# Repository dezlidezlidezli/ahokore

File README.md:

# ahokore

Ahokore is a 36-key one-piece split keyboard, with full wireless functionality. Stagger is copied from the Ferris, as I found that very comfortable. The name is "wireless" translated into Maori.

V1 is tested to be fully working, and uses a nice!nano.

V2 has been tested and is fully working, and a small group-buy has been run. Extras will be available within a few weeks (written on 30/6/21), on store.dez.li.

If you'd like to produce the board yourself, or modify these files, I reccomend using the v2-fantail

All work in this repository is released into the public domain. See the license file for more details!

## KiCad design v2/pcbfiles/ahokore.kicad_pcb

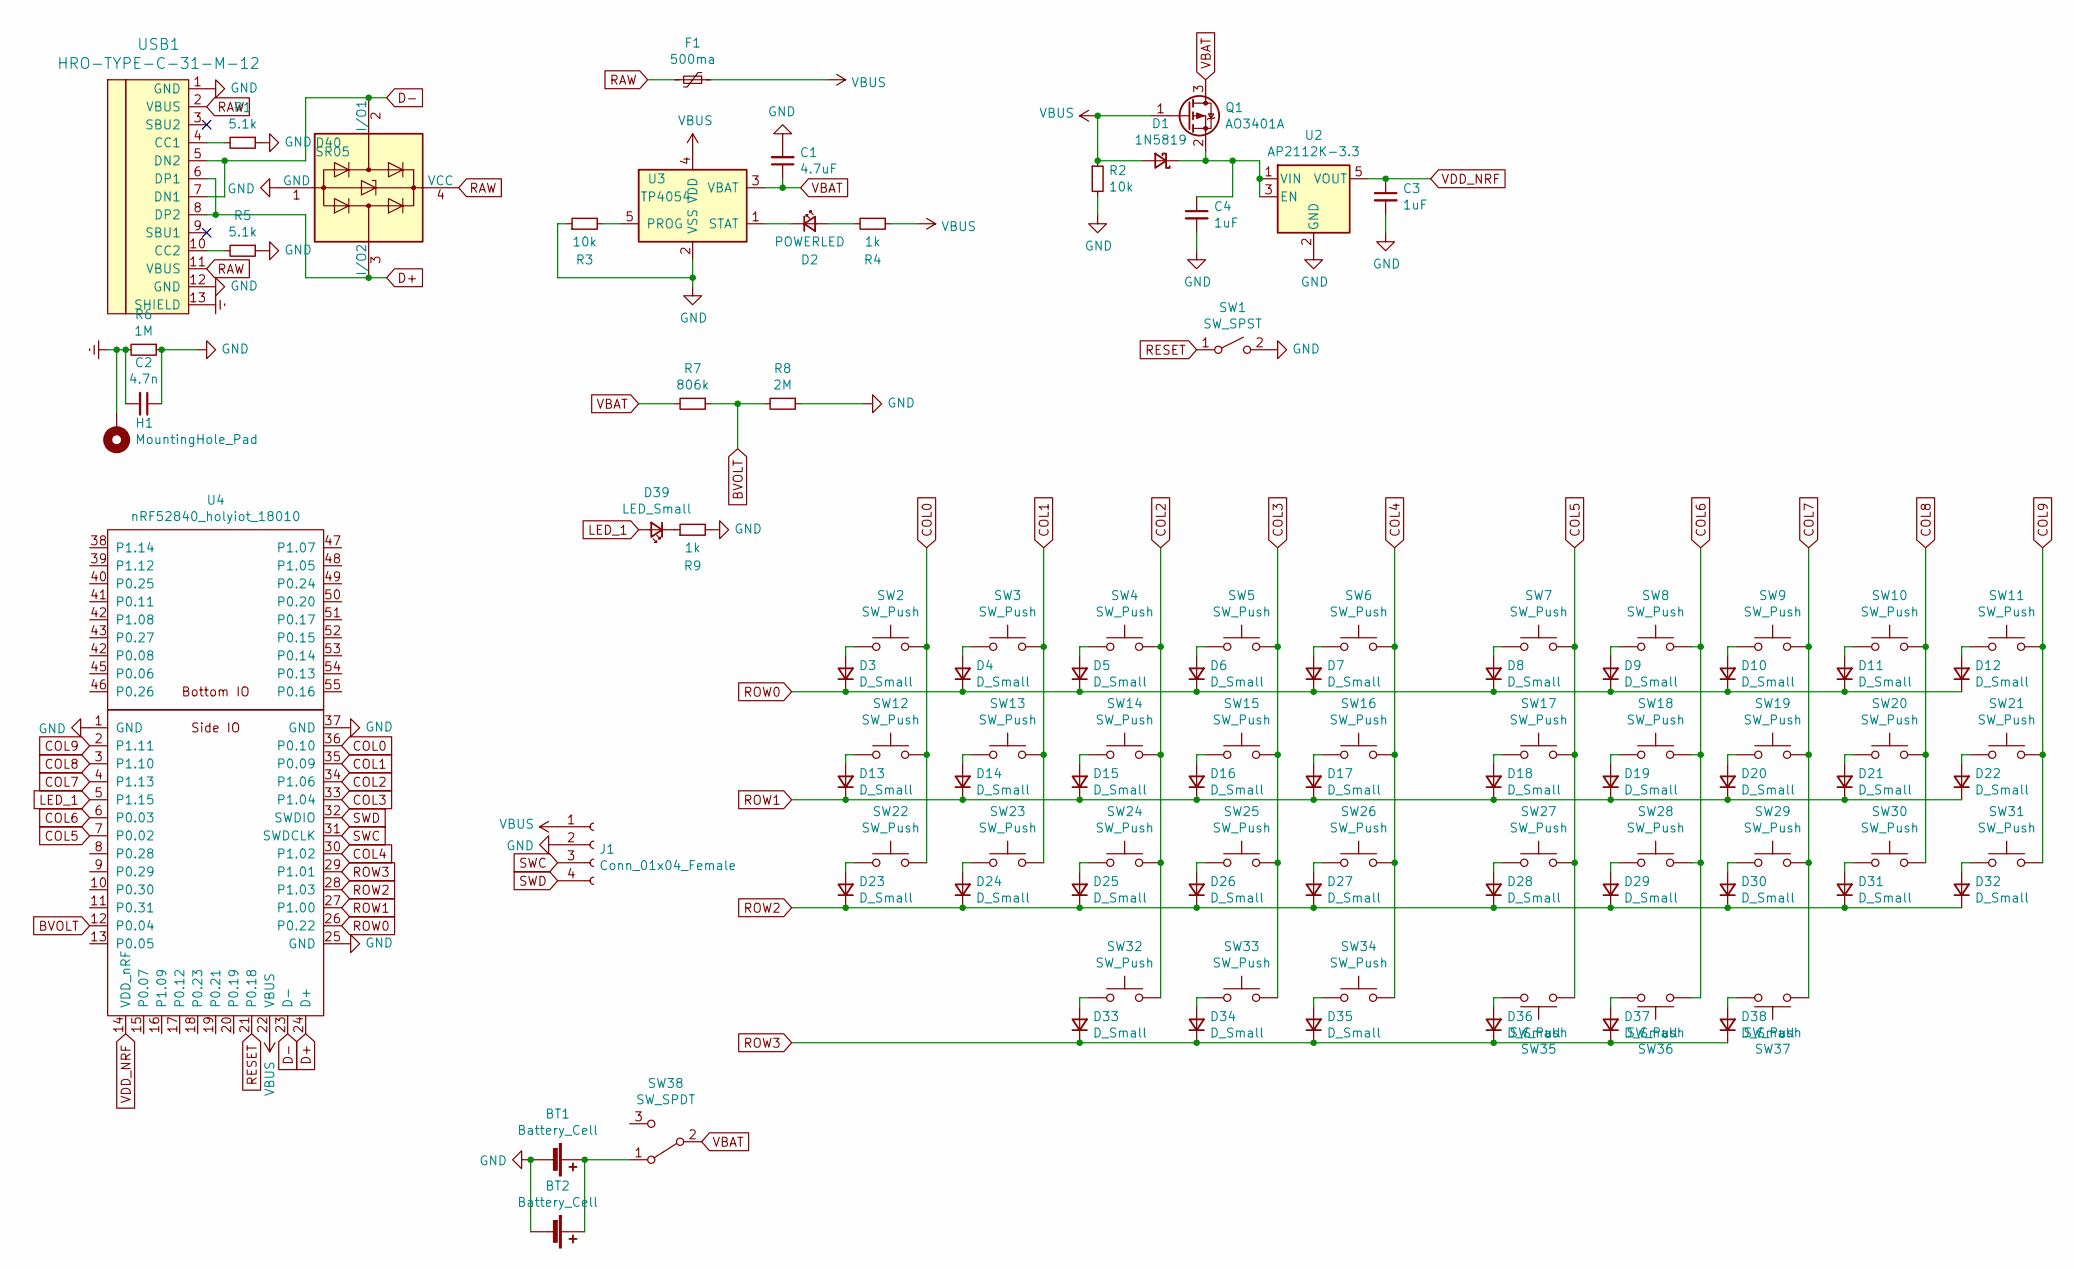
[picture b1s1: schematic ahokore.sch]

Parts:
BT1: Battery_Cell; JST_PH_S2B-PH-K_1x02_P2.00mm_Horizontal
BT2: Battery_Cell; custombatteryconnector
C1: 4.7uF; C_0805_2012Metric
C2: 4.7n; C_1206_3216Metric
C3, C4: 1uF; C_0805_2012Metric
D1: 1N5819; D_SOD-123
D2: POWERLED; D_0805_2012Metric
D3, D4, D5, D6, D7, D8, D9, D10, D11, D12, D13, D14, D15, D16, D17, D18, D19, D20, D21, D22, D23, D24, D25, D26, D27, D28, D29, D30, D31, D32, D33, D34, D35, D36, D37, D38: D_Small; D_SOD-123
D39: LED_Small; D_0805_2012Metric
D40: SR05; SOT-143
F1: 500ma; Fuse_1206_3216Metric
H1: MountingHole_Pad
J1: Conn_01x04_Female; PinHeader_1x04_P2.54mm_Vertical
Q1: AO3401A; SOT-23
R1, R5: 5.1k; R_0805_2012Metric
R2, R3: 10k; R_0805_2012Metric
R4, R9: 1k; R_0805_2012Metric
R6: 1M; R_0805_2012Metric
R7: 806k; R_0805_2012Metric
R8: 2M; R_0805_2012Metric
SW1: SW_SPST; custom-reset-switch
SW2, SW3, SW4, SW5, SW6, SW7, SW8, SW9, SW10, SW11, SW12, SW13, SW14, SW15, SW16, SW17, SW18, SW19, SW20, SW21, SW22, SW23, SW24, SW25, SW26, SW27, SW28, SW29, SW30, SW31, SW32, SW33, SW34, SW35, SW36, SW37: SW_Push; Choc_PG1350_Choc_Spacing
SW38: SW_SPDT; OS102011MA1QN1
U2: AP2112K-3.3; SOT-23-5
U3: TP4054; SOT-23-5
U4: nRF52840_holyiot_18010
USB1: HRO-TYPE-C-31-M-12; HRO-TYPE-C-31-M-12-HandSoldering

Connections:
BVOLT: R7.1, R8.2, U4.12 (P0.04)
COL0: SW2.2, SW12.2, SW22.2, U4.36 (P0.10)
COL1: SW3.2, SW13.2, SW23.2, U4.35 (P0.09)
COL2: SW4.2, SW14.2, SW24.2, SW32.2, U4.34 (P1.06)
COL3: SW5.2, SW15.2, SW25.2, SW33.2, U4.33 (P1.04)
COL4: SW6.2, SW16.2, SW26.2, SW34.2, U4.30 (P1.02)
COL5: SW7.2, SW17.2, SW27.2, SW35.1, U4.7 (P0.02)
COL6: SW8.2, SW18.2, SW28.2, SW36.1, U4.6 (P0.03)
COL7: SW9.2, SW19.2, SW29.2, SW37.1, U4.4 (P1.13)
COL8: SW10.2, SW20.2, SW30.2, U4.3 (P1.10)
COL9: SW11.2, SW21.2, SW31.2, U4.2 (P1.11)
D+: D40.3 (I/O2), U4.24 (D+), USB1.6 (DP1), USB1.8 (DP2)
D-: D40.2 (I/O1), U4.23 (D-), USB1.5 (DN2), USB1.7 (DN1)
Earth: C2.2, H1.1, R6.2, SW38.0, USB1.13 (SHIELD)
GND: BT1.2 (-), BT2.2 (-), C1.2, C2.1, C3.2, C4.2, D40.1 (GND), J1.2, R1.1, R2.2, R3.1, R5.1, R6.1, R8.1, R9.2, SW1.2 (B), U2.2 (GND), U3.2 (VSS), U4.1 (GND), U4.25 (GND), U4.37 (GND), USB1.1 (GND), USB1.12 (GND)
LED_1: D39.2 (A), U4.5 (P1.15)
unnamed: BT1.1 (+), BT2.1 (+), SW38.1 (A)
unnamed: C4.1, D1.1 (K), Q1.2 (S), U2.1 (VIN), U2.3 (EN)
unnamed: D2.1 (K), U3.1 (STAT)
unnamed: D2.2 (A), R4.2
unnamed: D3.2 (A), SW2.1
unnamed: D4.2 (A), SW3.1
unnamed: D5.2 (A), SW4.1
unnamed: D6.2 (A), SW5.1
unnamed: D7.2 (A), SW6.1
unnamed: D8.2 (A), SW7.1
unnamed: D9.2 (A), SW8.1
unnamed: D10.2 (A), SW9.1
unnamed: D11.2 (A), SW10.1
unnamed: D12.2 (A), SW11.1
unnamed: D13.2 (A), SW12.1
unnamed: D14.2 (A), SW13.1
unnamed: D15.2 (A), SW14.1
unnamed: D16.2 (A), SW15.1
unnamed: D17.2 (A), SW16.1
unnamed: D18.2 (A), SW17.1
unnamed: D19.2 (A), SW18.1
unnamed: D20.2 (A), SW19.1
unnamed: D21.2 (A), SW20.1
unnamed: D22.2 (A), SW21.1
unnamed: D23.2 (A), SW22.1
unnamed: D24.2 (A), SW23.1
unnamed: D25.2 (A), SW24.1
unnamed: D26.2 (A), SW25.1
unnamed: D27.2 (A), SW26.1
unnamed: D28.2 (A), SW27.1
unnamed: D29.2 (A), SW28.1
unnamed: D30.2 (A), SW29.1
unnamed: D31.2 (A), SW30.1
unnamed: D32.2 (A), SW31.1
unnamed: D33.2 (A), SW32.1
unnamed: D34.2 (A), SW33.1
unnamed: D35.2 (A), SW34.1
unnamed: D36.2 (A), SW35.2
unnamed: D37.2 (A), SW36.2
unnamed: D38.2 (A), SW37.2
unnamed: D39.1 (K), R9.1
unnamed: R1.2, USB1.4 (CC1)
unnamed: R3.2, U3.5 (PROG)
unnamed: R5.2, USB1.10 (CC2)
RAW: D40.4 (VCC), F1.2, USB1.2 (VBUS), USB1.11 (VBUS)
RESET: SW1.1 (A), U4.21 (P0.18)
ROW0: D3.1 (K), D4.1 (K), D5.1 (K), D6.1 (K), D7.1 (K), D8.1 (K), D9.1 (K), D10.1 (K), D11.1 (K), D12.1 (K), U4.26 (P0.22)
ROW1: D13.1 (K), D14.1 (K), D15.1 (K), D16.1 (K), D17.1 (K), D18.1 (K), D19.1 (K), D20.1 (K), D21.1 (K), D22.1 (K), U4.27 (P1.00)
ROW2: D23.1 (K), D24.1 (K), D25.1 (K), D26.1 (K), D27.1 (K), D28.1 (K), D29.1 (K), D30.1 (K), D31.1 (K), D32.1 (K), U4.28 (P1.03)
ROW3: D33.1 (K), D34.1 (K), D35.1 (K), D36.1 (K), D37.1 (K), D38.1 (K), U4.29 (P1.01)
SWC: J1.3, U4.31 (SWDCLK)
SWD: J1.4, U4.32 (SWDIO)
VBAT: C1.1, Q1.3 (D), R7.2, SW38.2 (B), U3.3 (VBAT)
VBUS: D1.2 (A), F1.1, J1.1, Q1.1 (G), R2.1, R4.1, U3.4 (VDD), U4.22 (VBUS)
VDD_NRF: C3.1, U2.5 (VOUT), U4.14 (VDD_nRF)

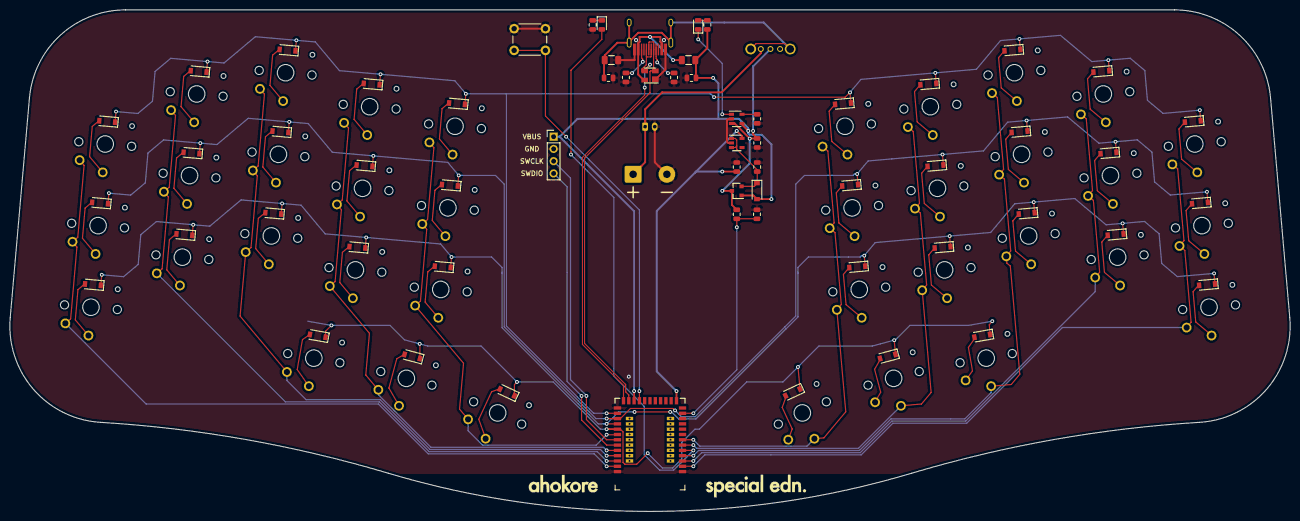
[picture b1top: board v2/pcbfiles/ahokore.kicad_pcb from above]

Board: 2 copper layers, 265.7 x 104.1 mm, 100 parts (0 on the bottom side), 71 nets.

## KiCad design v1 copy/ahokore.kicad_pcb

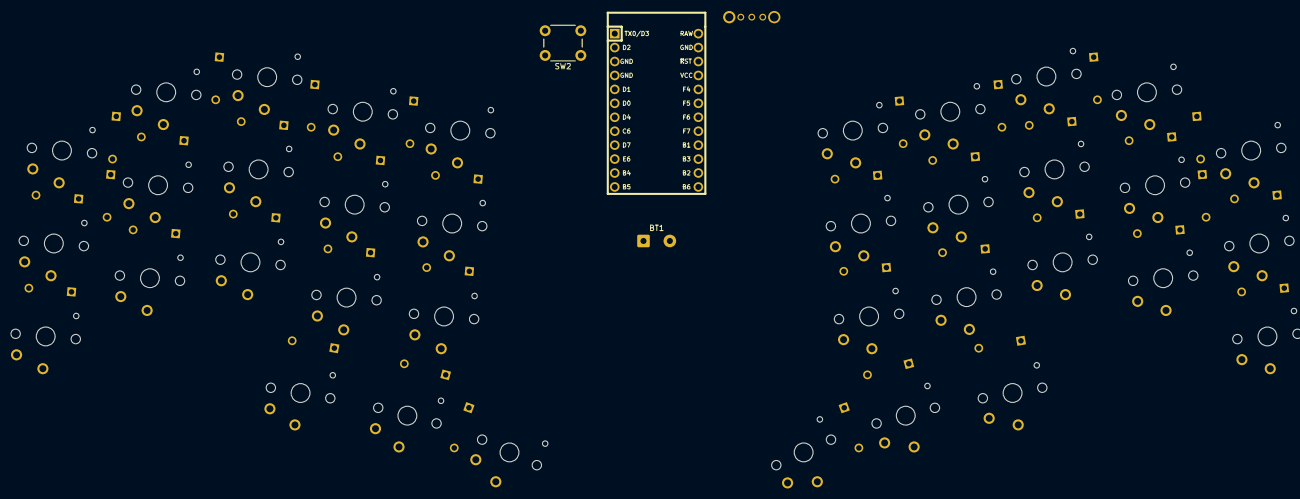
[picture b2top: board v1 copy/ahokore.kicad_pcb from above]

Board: 2 copper layers, 76 parts (0 on the bottom side), 54 nets, no tracks yet.

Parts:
BT1: Battery_Cell; battery
D1, D2, D3, D4, D5, D6, D7, D8, D9, D10, D11, D12, D13, D14, D15, D16, D17, D18, D19, D20, D21, D22, D23, D24, D25, D26, D27, D28, D29, D30, D31, D32, D33, D34, D35, D36: D_Small; Diode-Hybrid-Back
SW1: SW_SPDT; OS102011MA1QN1
SW2: SW_Push; SW_PUSH_6mm
SW3, SW4, SW5, SW6, SW7, SW8, SW9, SW10, SW11, SW12, SW13, SW14, SW15, SW16, SW17, SW18, SW19, SW20, SW21, SW22, SW23, SW24, SW25, SW26, SW27, SW28, SW29, SW30, SW31, SW32, SW33, SW34, SW35, SW36, SW37, SW38: SW_Push; Choc_PG1350_Choc_Spacing
U1: ProMicro; ArduinoProMicro

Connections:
+BATT: SW1.2, U1.24
COL0: SW3.2, SW13.2, SW23.2, U1.1
COL1: SW4.2, SW14.2, SW24.2, U1.2
COL2: SW5.2, SW15.2, SW25.2, SW33.2, U1.5
COL3: SW6.2, SW16.2, SW26.2, SW34.2, U1.6
COL4: SW7.2, SW17.2, SW27.2, SW35.2, U1.7
COL5: SW8.2, SW18.2, SW28.2, SW36.2, U1.20
COL6: SW9.2, SW19.2, SW29.2, SW37.2, U1.19
COL7: SW10.2, SW20.2, SW30.2, SW38.2, U1.18
COL8: SW11.2, SW21.2, SW31.2, U1.17
COL9: SW12.2, SW22.2, SW32.2, U1.16
GND: BT1.2, SW2.2, U1.3, U1.4, U1.23
unnamed: BT1.1, SW1.1
unnamed: D1.2, SW3.1
unnamed: D2.2, SW4.1
unnamed: D3.2, SW5.1
unnamed: D4.2, SW6.1
unnamed: D5.2, SW7.1
unnamed: D6.2, SW8.1
unnamed: D7.2, SW9.1
unnamed: D8.2, SW10.1
unnamed: D9.2, SW11.1
unnamed: D10.2, SW12.1
unnamed: D11.2, SW13.1
unnamed: D12.2, SW14.1
unnamed: D13.2, SW15.1
unnamed: D14.2, SW16.1
unnamed: D15.2, SW17.1
unnamed: D16.2, SW18.1
unnamed: D17.2, SW19.1
unnamed: D18.2, SW20.1
unnamed: D19.2, SW21.1
unnamed: D20.2, SW22.1
unnamed: D21.2, SW23.1
unnamed: D22.2, SW24.1
unnamed: D23.2, SW25.1
unnamed: D24.2, SW26.1
unnamed: D25.2, SW27.1
unnamed: D26.2, SW28.1
unnamed: D27.2, SW29.1
unnamed: D28.2, SW30.1
unnamed: D29.2, SW31.1
unnamed: D30.2, SW32.1
unnamed: D31.2, SW33.1
unnamed: D32.2, SW34.1
unnamed: D33.2, SW35.1
unnamed: D34.2, SW36.1
unnamed: D35.2, SW37.1
unnamed: D36.2, SW38.1
ROW0: D1.1, D2.1, D3.1, D4.1, D5.1, D6.1, D7.1, D8.1, D9.1, D10.1, U1.8
ROW1: D11.1, D12.1, D13.1, D14.1, D15.1, D16.1, D17.1, D18.1, D19.1, D20.1, U1.9
ROW2: D21.1, D22.1, D23.1, D24.1, D25.1, D26.1, D27.1, D28.1, D29.1, D30.1, U1.10
ROW3: D31.1, D32.1, D33.1, D34.1, D35.1, D36.1, U1.11
RST: SW2.1, U1.22

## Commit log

2020-10-20 add license
2020-10-20 add blank kicad files
2020-10-20 submodules
2020-10-20 kicad file updates
2020-10-20 layout pcb
2020-10-21 add diodes
2020-10-21 last commit before edgecuts
2020-10-21 nvm, not the last one
2020-10-22 routing half
2020-10-22 readyforfirstcheck
2020-10-22 finished, no checks yet
2020-10-22 i'm basically done :)
2020-10-29 production pcb files, silk and mounting holes add
2020-10-29 rename
2020-10-29 slight updates
2020-10-29 i forgot to save before updates
2020-12-09 stuff :)
2020-12-09 formatting of repo update
2020-12-09 add photos and gerbers
2021-01-25 wooohoooo
2021-02-27 production
2021-06-30 megacommit
2021-06-30 readme
2021-06-30 yeet
2021-07-03 add bottom plate files
2021-07-05 stuff
